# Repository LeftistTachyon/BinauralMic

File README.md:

# Tachi's Homemade Binaural Mic
More to come soon!  
(I barely have a schematic atm lol)

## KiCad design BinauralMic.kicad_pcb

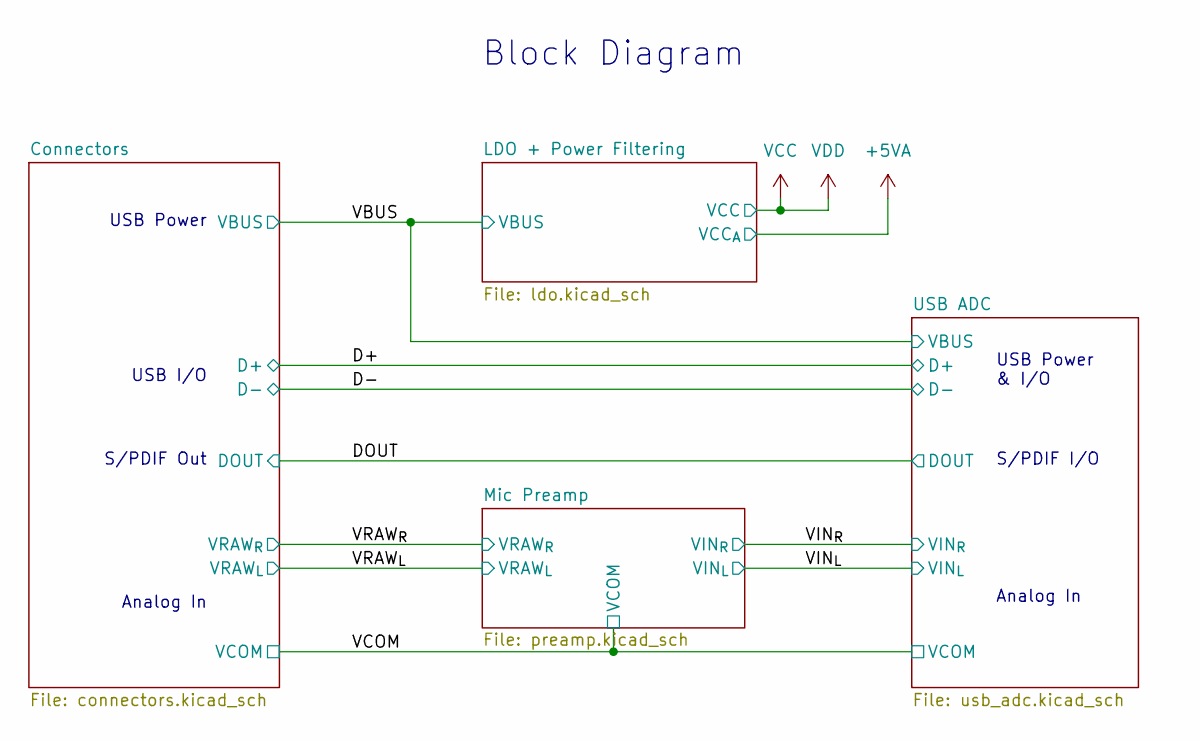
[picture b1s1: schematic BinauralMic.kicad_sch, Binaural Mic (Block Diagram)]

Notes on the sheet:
Analog In
USB Power
S/PDIF I/O
USB I/O
USB Power & I/O
S/PDIF Out
Block Diagram

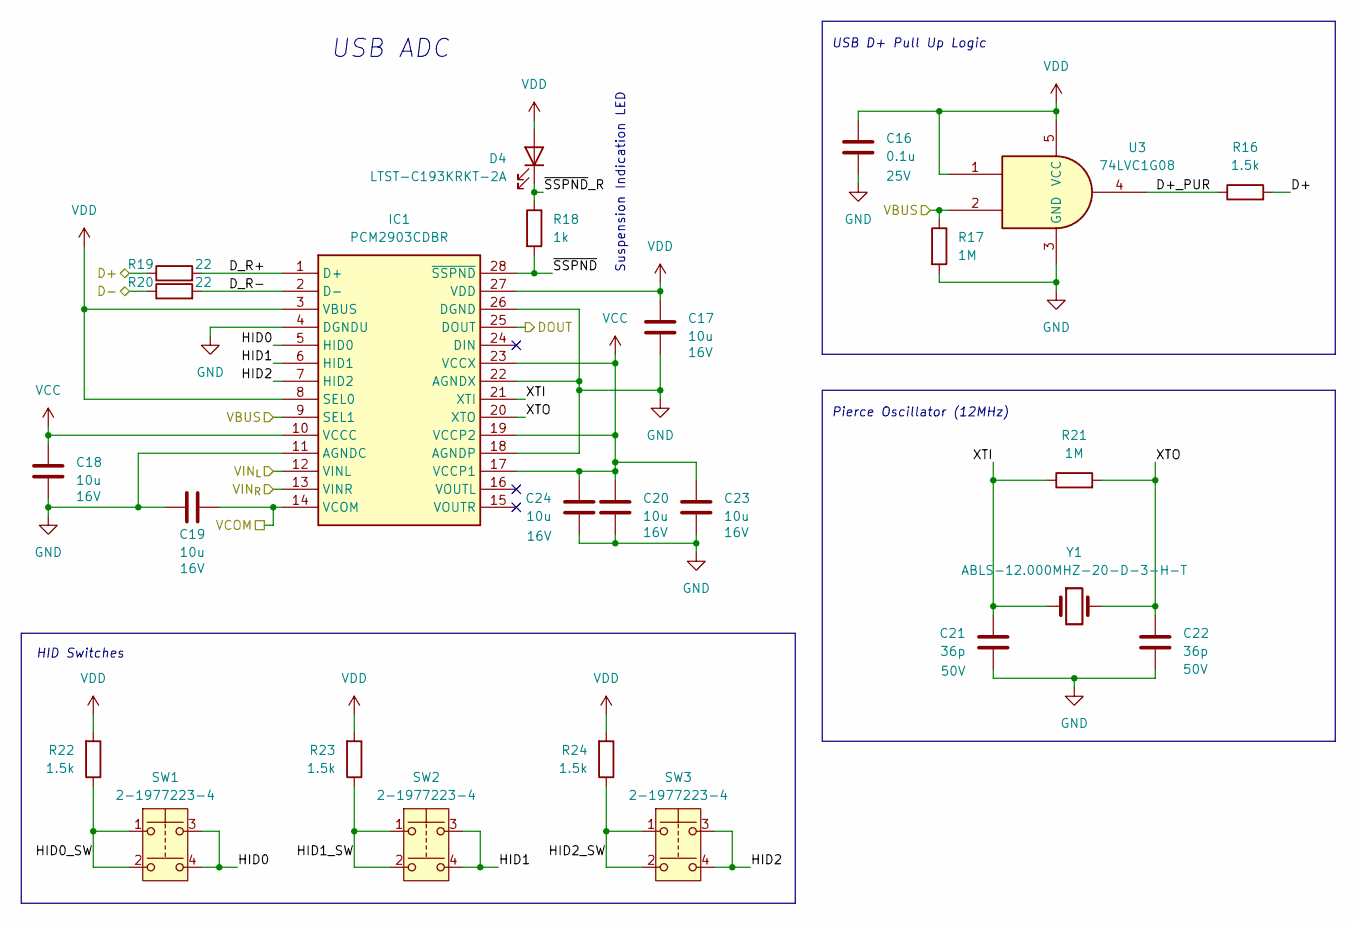
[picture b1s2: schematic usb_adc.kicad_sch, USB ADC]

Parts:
C16: 0.1u; C_0603_1608Metric_Pad1.08x0.95mm_HandSolder; Voltage Rating 25V; Mouser Part Number 187-CL10A104KA8NNNC
C17, C18, C19, C20, C23, C24: 10u; C_1206_3216Metric_Pad1.33x1.80mm_HandSolder; Voltage Rating 16V; Mouser Part Number 581-TAJA106K016R
C21, C22: 36p; C_0603_1608Metric_Pad1.08x0.95mm_HandSolder; Voltage Rating 50V; Mouser Part Number 603-CC603FRNPO9BN360
D4: LTST-C193KRKT-2A; LED_0603_1608Metric_Pad1.05x0.95mm_HandSolder; Mouser Part Number 859-LTST-C193KRKT-2A
IC1: PCM2903CDBR; SOP65P780X200-28N; Mouser Part Number 595-PCM2903CDBR
R16, R22, R23, R24: 1.5k; R_0603_1608Metric_Pad0.98x0.95mm_HandSolder; Mouser Part Number 667-ERA-3AEB152V
R17, R21: 1M; R_0603_1608Metric_Pad0.98x0.95mm_HandSolder; Mouser Part Number 652-CR0603FX-1004ELF
R18: 1k; R_0603_1608Metric_Pad0.98x0.95mm_HandSolder; Mouser Part Number 71-CRCW06031K00FKEE
R19, R20: 22; R_0603_1608Metric_Pad0.98x0.95mm_HandSolder; Mouser Part Number 652-CR0603FX-22R0ELF
SW1, SW2, SW3: 2-1977223-4; 219772234
U3: 74LVC1G08; SOT-23-5_HandSoldering; Mouser Part Number 771-74LVC1G08GV
Y1: ABLS-12.000MHZ-20-D-3-H-T; ABLS; Mouser Part Number 815-LS12000MHZ20D3HT

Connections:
/D+: R16.2, R19.1; also elsewhere on the board
/D-: R20.1; also elsewhere on the board
/DOUT: IC1.25 (DOUT)
/USB ADC/D+_PUR: R16.1, U3.4
/USB ADC/D_R+: IC1.1 (D+), R19.2
/USB ADC/D_R-: IC1.2 (D-), R20.2
/USB ADC/HID0: IC1.5 (HID0), SW1.3, SW1.4
/USB ADC/HID0_SW: R22.1, SW1.1, SW1.2
/USB ADC/HID1: IC1.6 (HID1), SW2.3, SW2.4
/USB ADC/HID1_SW: R23.1, SW2.1, SW2.2
/USB ADC/HID2: IC1.7 (HID2), SW3.3, SW3.4
/USB ADC/HID2_SW: R24.1, SW3.1, SW3.2
/USB ADC/XTI: C21.1, IC1.21 (XTI), R21.1, Y1.1
/USB ADC/XTO: C22.1, IC1.20 (XTO), R21.2, Y1.2
/USB ADC/~SSPND: IC1.28 (~SSPND), R18.2
/USB ADC/~SSPND_R: D4.1 (K), R18.1
/VBUS: IC1.9 (SEL1), R17.1, U3.2; also elsewhere on the board
/VCOM: C19.2, IC1.14 (VCOM); also elsewhere on the board
/VIN_{L}: IC1.12 (VINL); also elsewhere on the board
/VIN_{R}: IC1.13 (VINR); also elsewhere on the board
GND: C16.1, C17.2, C18.2, C19.1, C20.2, C21.2, C22.2, C23.2, C24.2, IC1.4 (DGNDU), IC1.11 (AGNDC), IC1.18 (AGNDP), IC1.22 (AGNDX), IC1.26 (DGND), R17.2, U3.3 (GND); also elsewhere on the board

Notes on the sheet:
USB ADC
HID Switches
Pierce Oscillator (12MHz)
USB D+ Pull Up Logic
Suspension Indication LED

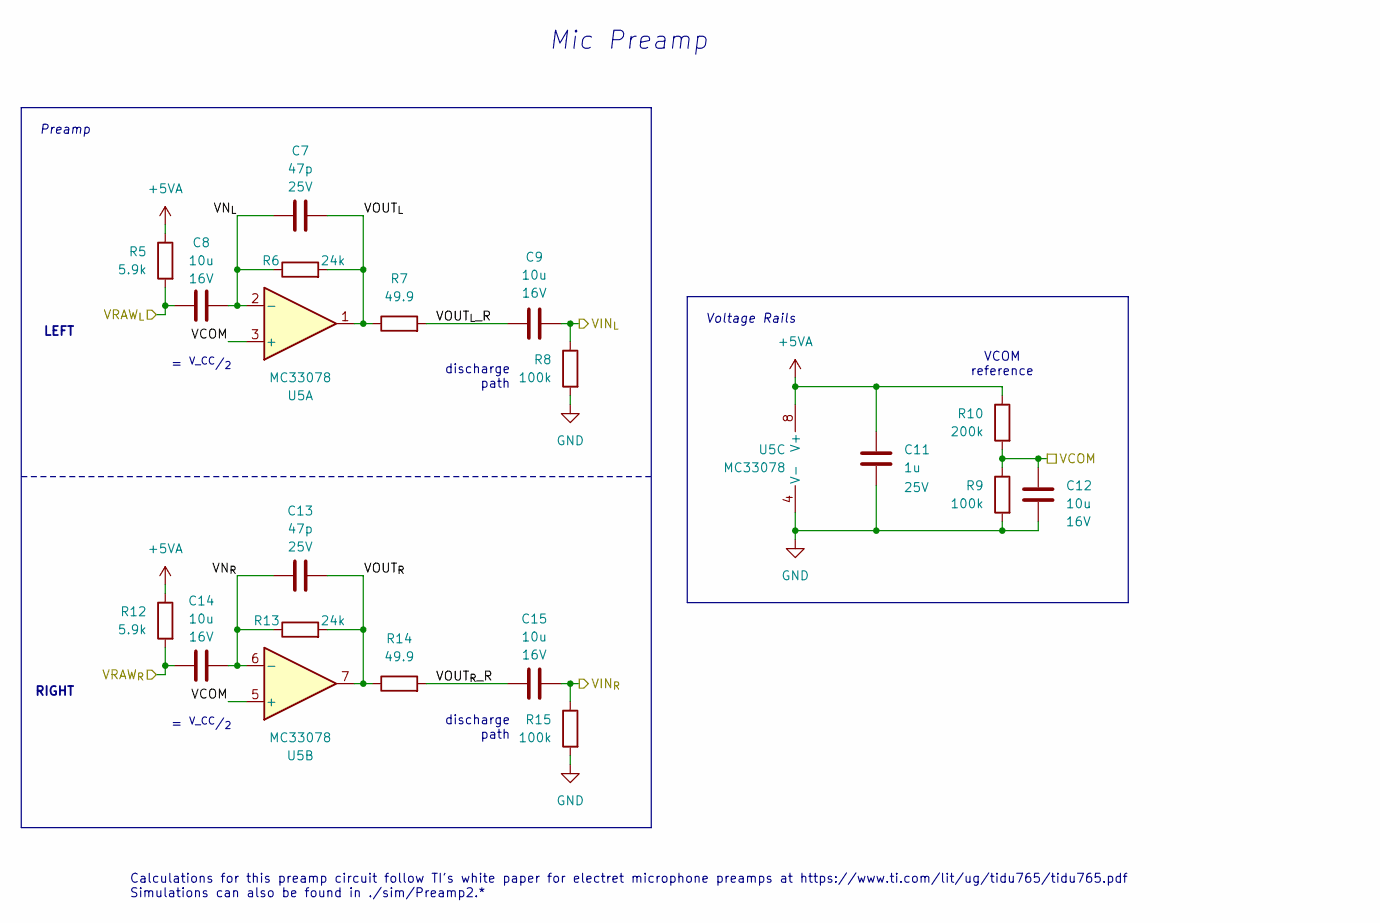
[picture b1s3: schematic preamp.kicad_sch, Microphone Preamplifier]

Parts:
C7, C13: 47p; C_0603_1608Metric_Pad1.08x0.95mm_HandSolder; Voltage Rating 25V; Mouser Part Number 77-VJ0603A470JXXCBC
C8, C9, C12, C14, C15: 10u; C_1206_3216Metric_Pad1.33x1.80mm_HandSolder; Voltage Rating 16V; Mouser Part Number 581-TAJA106K016R
C11: 1u; C_0603_1608Metric_Pad1.08x0.95mm_HandSolder; Voltage Rating 25V; Mouser Part Number 187-CL10B105KA8NNNL
R5, R12: 5.9k; R_0603_1608Metric_Pad0.98x0.95mm_HandSolder; Mouser Part Number 667-ERA-3AEB5901V
R6, R13: 24k; R_0603_1608Metric_Pad0.98x0.95mm_HandSolder; Mouser Part Number 03-RT0603DRD0724KL
R7, R14: 49.9; R_0603_1608Metric_Pad0.98x0.95mm_HandSolder; Mouser Part Number 791-RMC1/16K49R9FTP
R8, R9, R15: 100k; R_0603_1608Metric_Pad0.98x0.95mm_HandSolder; Mouser Part Number 603-RT0603FRE10100KL
R10: 200k; R_0603_1608Metric_Pad0.98x0.95mm_HandSolder; Mouser Part Number 603-AF0603FR-07200KL
U5: MC33078; SOIC-8_3.9x4.9mm_P1.27mm; Mouser Part Number 863-MC33078DR2G

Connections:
+5VA: C11.1, R5.1, R10.1, R12.1, U5.8 (V+); also elsewhere on the board
/Mic Preamp/VN_{L}: C7.1, C8.2, R6.1, U5.2 (-)
/Mic Preamp/VN_{R}: C13.1, C14.2, R13.1, U5.6 (-)
/Mic Preamp/VOUT_{L}: C7.2, R6.2, R7.1, U5.1
/Mic Preamp/VOUT_{L}_R: C9.1, R7.2
/Mic Preamp/VOUT_{R}: C13.2, R13.2, R14.1, U5.7
/Mic Preamp/VOUT_{R}_R: C15.1, R14.2
/VCOM: C12.2, R9.1, R10.2, U5.3 (+), U5.5 (+); also elsewhere on the board
/VIN_{L}: C9.2, R8.1; also elsewhere on the board
/VIN_{R}: C15.2, R15.1; also elsewhere on the board
/VRAW_{L}: C8.1, R5.2; also elsewhere on the board
/VRAW_{R}: C14.1, R12.2; also elsewhere on the board
GND: C11.2, C12.1, R8.2, R9.2, R15.2, U5.4 (V-); also elsewhere on the board

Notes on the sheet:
RIGHT
= ^{V_CC}/_{2}
LEFT
Mic Preamp
discharge path
VCOM reference
Calculations for this preamp circuit follow TI's white paper for electret microphone preamps at https://www.ti.com/lit/ug/tidu765/tidu765.pdf Simulations can also be found in ./sim/Preamp2.*
Voltage Rails
Preamp

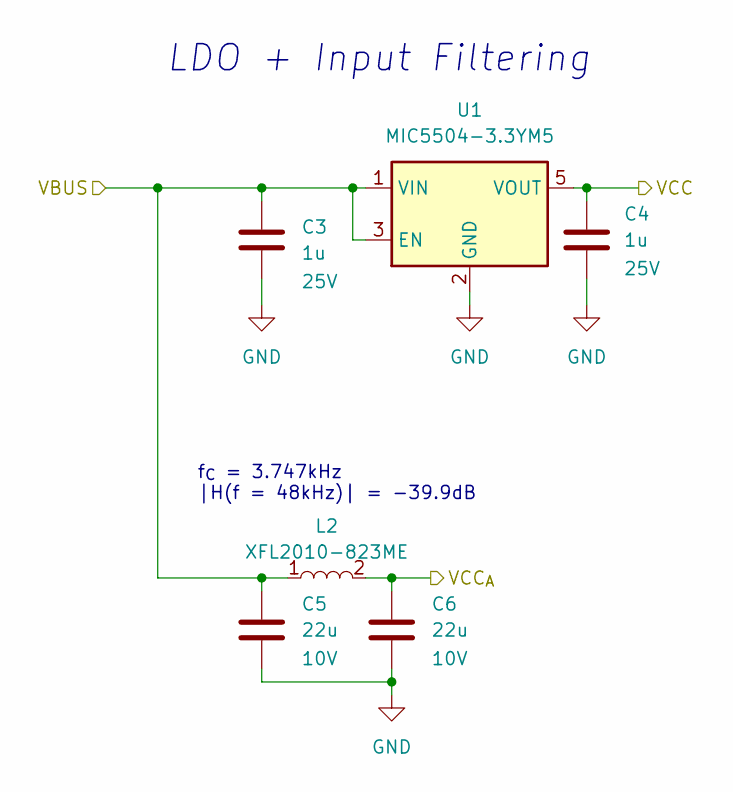
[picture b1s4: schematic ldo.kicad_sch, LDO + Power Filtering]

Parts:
C3, C4: 1u; C_0603_1608Metric_Pad1.08x0.95mm_HandSolder; Voltage Rating 25V; Mouser Part Number 187-CL10B105KA8NNNL
C5, C6: 22u; C_0805_2012Metric_Pad1.18x1.45mm_HandSolder; Voltage Rating 10V; Mouser Part Number 187-CL21A226MPQNNNE
L2: XFL2010-823ME; L_Coilcraft_XFL2010
U1: MIC5504-3.3YM5; SOT-23-5_HandSoldering; Mouser Part Number 998-MIC5504-3.3YM5TR

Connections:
+5VA: C6.1, L2.2; also elsewhere on the board
/VBUS: C3.1, C5.1, L2.1, U1.1 (VIN), U1.3 (EN); also elsewhere on the board
GND: C3.2, C4.2, C5.2, C6.2, U1.2 (GND); also elsewhere on the board

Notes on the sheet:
f_{C} = 3.747kHz |H(f = 48kHz)| = -39.9dB
LDO + Input Filtering

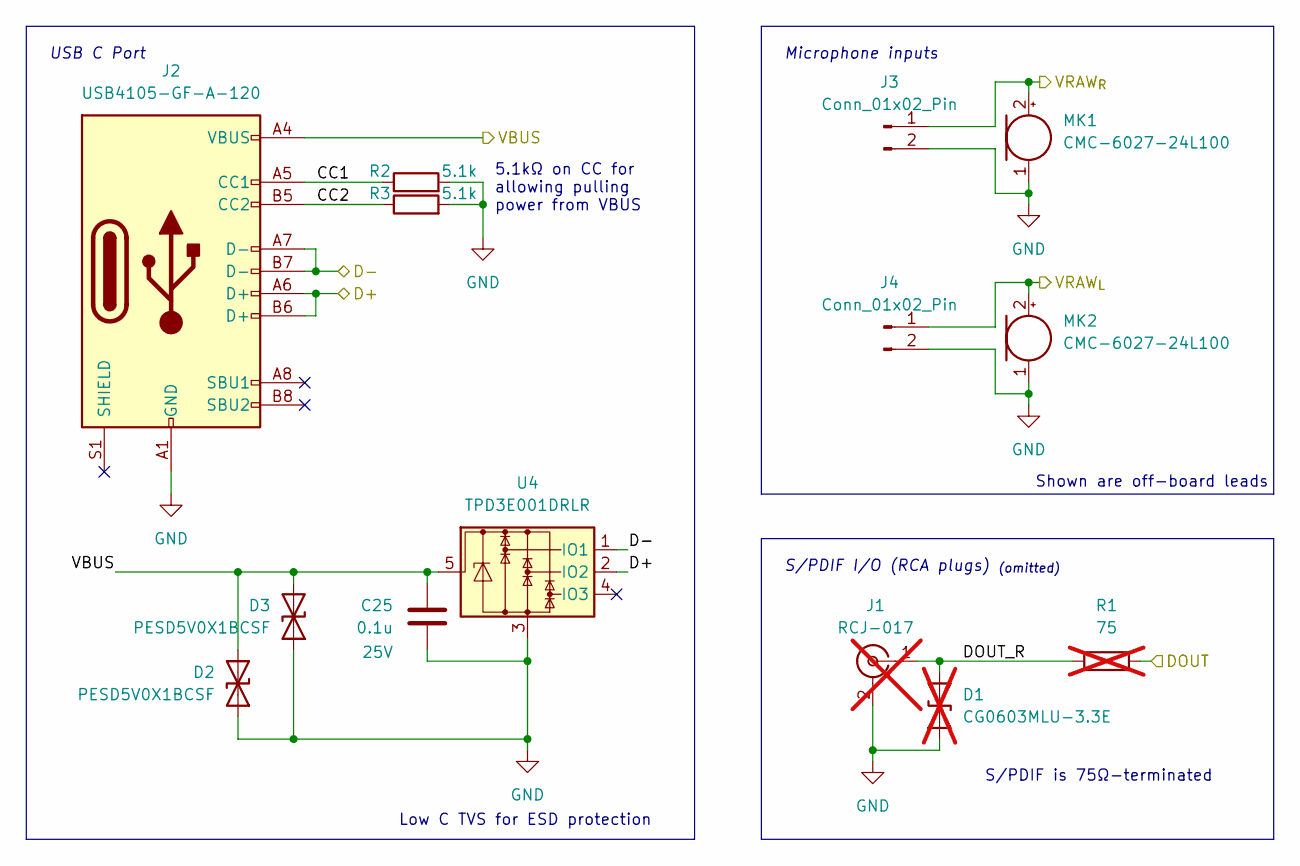
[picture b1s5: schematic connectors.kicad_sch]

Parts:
C25: 0.1u; C_0603_1608Metric_Pad1.08x0.95mm_HandSolder; Voltage Rating 25V; Mouser Part Number 187-CL10A104KA8NNNC
D1: CG0603MLU-3.3E; D_0603_1608Metric_Pad1.05x0.95mm_HandSolder; Mouser Part Number 652-CG0603MLU-3.3E; not fitted
D2, D3: PESD5V0X1BCSF; D_0603_1608Metric_Pad1.05x0.95mm_HandSolder; Mouser Part Number 771-PESD5V0X1BCSFYL
J1: RCJ-017; RCJ014; Mouser Part Number 490-RCJ-017; not fitted
J2: USB4105-GF-A-120; USB_C_Receptacle_GCT_USB4085; Mouser Part Number 640-USB4085-GF-A
J3, J4: Conn_01x02_Pin; PinHeader_1x02_P2.00mm_Vertical
MK1, MK2: CMC-6027-24L100; Mouser Part Number 490-CMC-6027-24L100
R1: 75; R_0603_1608Metric_Pad0.98x0.95mm_HandSolder; Mouser Part Number 603-RT0603FRE0775RL; not fitted
R2, R3: 5.1k; R_0603_1608Metric_Pad0.98x0.95mm_HandSolder; Mouser Part Number 603-RC0603FR-105K1L
U4: TPD3E001DRLR; SOT-553; Mouser Part Number 595-TPD3E001DRLR

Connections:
/Connectors/CC1: J2.A5 (CC1), R2.1
/Connectors/CC2: J2.B5 (CC2), R3.1
/D+: J2.A6 (D+), J2.B6 (D+), U4.2 (IO2); also elsewhere on the board
/D-: J2.A7 (D-), J2.B7 (D-), U4.1 (IO1); also elsewhere on the board
/VBUS: C25.2, D2.2 (A2), D3.2 (A2), J2.A4 (VBUS), J2.A9 (VBUS), J2.B4 (VBUS), J2.B9 (VBUS), U4.5; also elsewhere on the board
/VRAW_{L}: J4.1, MK2.2 (+); also elsewhere on the board
/VRAW_{R}: J3.1, MK1.2 (+); also elsewhere on the board
GND: C25.1, D1.1 (A1), D2.1 (A1), D3.1 (A1), J1.2 (Ext), J2.A1 (GND), J2.A12 (GND), J2.B1 (GND), J2.B12 (GND), J3.2, J4.2, MK1.1 (-), MK2.1 (-), R2.2, R3.2, U4.3; also elsewhere on the board
unnamed: D1.2 (A2), J1.1 (In), R1.2

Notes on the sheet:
USB C Port
S/PDIF is 75Ω-terminated
Shown are off-board leads
Microphone inputs
S/PDIF I/O (RCA plugs) _{(omitted)}
5.1kΩ on CC for allowing pulling power from VBUS
Low C TVS for ESD protection

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
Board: 2 copper layers, 59 parts (0 on the bottom side), 32 nets, no tracks yet.

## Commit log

2024-09-13 First commit
    Adding .gitignore to ignore the useless files first
2024-09-13 Add project files
2024-09-13 Add USB port
2024-09-13 Organization
2024-09-14 Added input filter
    LTSpice simulation to come soon
2024-09-14 Adding input filter LTSpice simulation file
2024-09-14 Add various things
2024-09-15 Add simulations and new op amp preamp
    And hand calcs
2024-09-15 Copy the correct values from the hand calcs & copy to simulations
2024-09-15 Move files to sim folder
2024-09-15 Reorganized schematic
    Should be much cleaner now
    And added a random shunt resistor to measure current coming out of Op Amp (should be ok)
2024-09-15 Save unchanged changes
2024-09-15 Resnap text to grid + add .gitignore
2024-09-15 Started defining components
    Man going down the capacitor dielectric rabbit hole eats up SO MUCH TIME
2024-09-15 Fully define components
2024-09-15 Replace S/PIDF RCA jack with a singular one since I won't need an input one
2024-09-16 Removing extraneous peripherals
2024-09-16 Add analog volume control
2024-09-16 Remove potentiometer
    Will have to find a different solution for volume control
    Just do it OS-side?
2024-09-16 Starting layout
    Also why are the mf diodes so small
2024-09-17 Started layout?
2024-09-21 Marginal changes
2024-09-21 Replace 0201 diodes with recommended arrays and nothing (some were spurious and I think I don't need them)
2024-09-21 Reannotated schematic + restarted layout
    woohoo
2024-09-21 Add more detailed RCJ-014 model + shifting things around
    Also added another ESD diode for VBUS because only one will be connected for USB C :/
2024-09-21 Removed S/PIDF and still doing layout
2024-09-22 More layout, replaced chip crystal with a 2-pin oscillator
    All is well with the world
2024-09-22 Layout changes
    See previous commit
    I forgot to save lol
2024-09-22 Did a lot of layout
2024-09-22 Flipped inductor direction (dot towards EMI) and shuffled some components around
    Hopefully a more rested me can fit this jigsaw a little better
2024-10-03 Layout + routing for preamp
2024-10-04 Finished routing
2024-10-05 Passing review from @MorrisYLin
    Thank you for looking everything over!
2024-10-06 Add silkscreen + some bonus test points
2024-10-06 Ordered!
2024-10-06 Fix pierce osc load caps
2024-10-13 Add step file
2024-11-11 add ibom
2025-07-06 Redid schematic and component values according to new recalculations
2025-07-08 Add buttons for device control + various other changes
